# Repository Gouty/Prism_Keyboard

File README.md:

#  Prism Mechanical Keyboard

Prism is a low cost QMK compatable 60% + nav cluster (or TKL minus F-row if you prefer) keyboard.

It came about for a number of reasons:

 * I had some [TGW71 PCBs](https://www.reddit.com/r/MechanicalKeyboards/comments/5un33s/the_great_wave_custom_board/) designed by [u/ca178858](https://www.reddit.com/user/ca178858) lying around doing nothing
 * I am procrastinating instead of doing my PhD thesis writeup
 * There was a competition on [r/CustomKeyboards](https://www.reddit.com/r/CustomKeyboards/) to build retro themed keyboards.

As it was planned for the OG Summer competition I decided to emulate some of the design language of the [ZX Sepctrum](https://imgur.com/a/drfZssH) family of computers (particularly the the ones that came after the 48k).

## Initial Design document

## To Do

* Improve feet fastening/height adjustment
* Update .dxf to include latest revision

## Future Plans

Currently this repo is a bit of a dumping ground for what I have designed so far, though it is possible to recreate the keyboard entirely. Eventually I want it to include:

* Multiple plate layer configurations
* Multiple top layer configuations
* Changes to the PCB to include PCB mount stabilisers and better bottom row support

## Current status

Prototype complete - Displayed at Mechanical Keyboard Meetup (Leeds 26/10/2019)

## Posts about Prism

* [Initial](https://www.reddit.com/r/CustomKeyboards/comments/c7dlp8/ogsummer_zx_spectrum_inspired_work_in_progress/)
* [Update](https://www.reddit.com/r/CustomKeyboards/comments/cu45r6/ogsummer_prism_zx_spectrum_inspired_update/)
* [Keebtalk](https://www.keebtalk.com/t/prism-a-zx-spectrum-inspired-low-cost-acrylic-case/)
* [Prototype](https://www.reddit.com/r/MechanicalKeyboards/comments/dqqovr/rbgy/), [2](https://www.reddit.com/r/CustomKeyboards/comments/dqr5ce/prism_prototype/)

## Thanks

Original TGW71 PCB by [u/ca178858](https://www.reddit.com/user/ca178858) and [u/the_pokemon_kid](https://www.reddit.com/user/the_pokemon_kid)

Pixel art by Meowsaur

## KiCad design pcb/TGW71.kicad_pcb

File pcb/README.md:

# TGW71 PCB

Original files kindly provided by [u/ca178858](https://www.reddit.com/user/ca178858)

BOM:

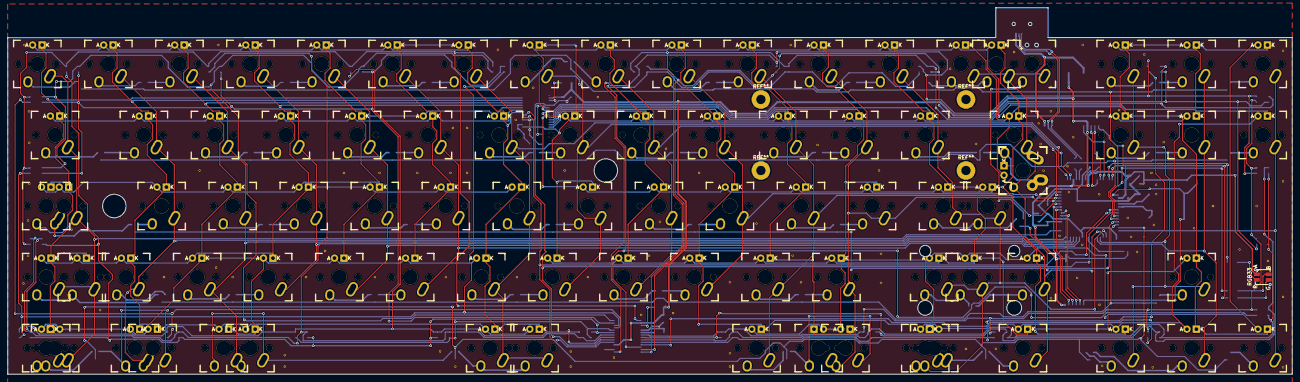
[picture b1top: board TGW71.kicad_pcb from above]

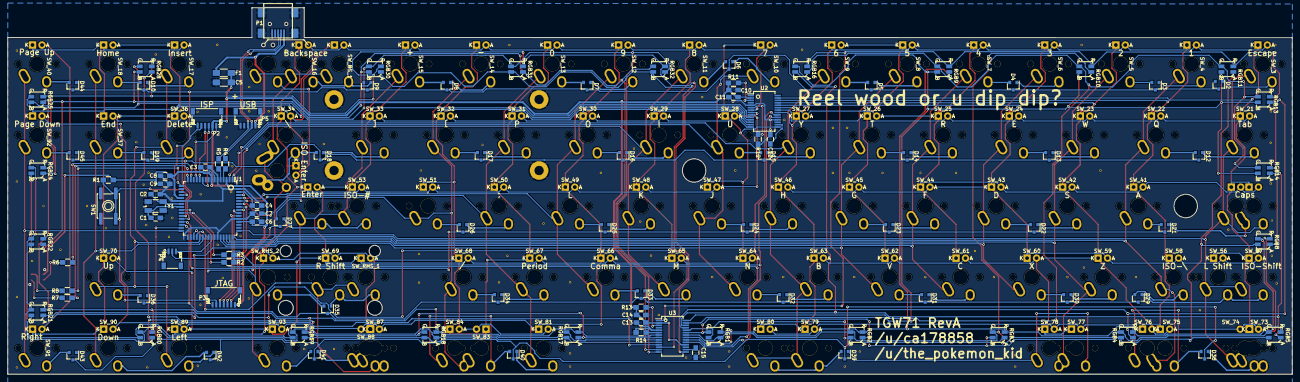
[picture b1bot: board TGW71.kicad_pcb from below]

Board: 2 copper layers, 344.5 x 98.3 mm, 192 parts (102 on the bottom side), 164 nets.

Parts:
C1, C2: 18pF; C_0805_HandSoldering
C3, C6, C7, C8, C9, C11, C12, C14, C15: 0.1µF; C_0805_HandSoldering
C4, C10, C13: 1µF; C_0805_HandSoldering
C5: 4.7µF; C_1206_HandSoldering
D2, D3, D4, D5, D6, D7, D8, D9, D10, D12, D13, D14, D15, D16, D17, D18, D19, D21, D22, D23, D24, D25, D26, D27, D29, D30, D31, D32, D33, D34, D35, D36, D38, D39, D40, D41, D42, D43, D44, D45: BAV70L; SOT-23
F1: FP_Small; C_1206_HandSoldering
P1: USB_OTG; USB_Mini-B
P2: CONN_02X03; JST_SH_SM06B-SRSS-TB_06x1.00mm_Angled
P3: CONN_01X07; JST_SH_SM07B-SRSS-TB_07x1.00mm_Angled
P4: CONN_01X03; JST_SH_SM03B-SRSS-TB_03x1.00mm_Angled
P5: CONN_01X05; JST_SH_SM05B-SRSS-TB_05x1.00mm_Angled
R1: 10kΩ; R_0805_HandSoldering
R2, R3: 4.7kΩ; R_0805_HandSoldering
R4, R5: 22Ω; R_0805_HandSoldering
R6: 150; R_0805_HandSoldering
R7, R8: 120; R_0805_HandSoldering
R11, R13: 10KΩ; R_0805_HandSoldering
R12, R14: 20KΩ; R_0805_HandSoldering
RGB1, RGB2, RGB3, RGB4, RGB5, RGB8, RGB9, RGB10, RGB11, RGB13, RGB14, RGB16, RGB17, RGB18, RGB19, RGB20, RGB21, RGB22, RGB24, RGB25, RGB28, RGB30, RGB31, RGB32: Led_RGB_CA; SMP4-RGB
RGB33: Led_RGB_CA; SMP4-RGB-PIPE
STA: Stabilizer; CHERRY_PCB_200_STABILIZER_OUTLINE
STA#2: Stabilizer; CHERRY_PCB_200_STABILIZER
SW1: SW_PUSH; SW_SPST_EVQP0
SW_3, SW_4, SW_5, SW_6, SW_7, SW_8, SW_9, SW_10, SW_11, SW_12, SW_13, SW_14, SW_15, SW_16, SW_17, SW_18, SW_21, SW_22, SW_23, SW_24, SW_25, SW_26, SW_27, SW_28, SW_29, SW_30, SW_31, SW_32, SW_33, SW_34, SW_35, SW_36, SW_37, SW_40, SW_41, SW_42, SW_43, SW_44, SW_45, SW_46, SW_47, SW_48, SW_49, SW_50, SW_51, SW_52, SW_53, SW_56, SW_57, SW_58, SW_59, SW_60, SW_61, SW_62, SW_63, SW_64, SW_65, SW_66, SW_67, SW_68, SW_69, SW_70, SW_73, SW_75, SW_76, SW_77, SW_78, SW_79, SW_80, SW_81, SW_84, SW_87, SW_89, SW_90, SW_91, SW_92, SW_93: MX_LED; MXALPS
SW_74, SW_83, SW_88: MX_LED; MXALPS_REVERSE_LED
SW_BS_1, SW_BS_2: MX_LED; MXALPS
SW_CAPS_1, SW_CAPS_2: MX_LED; MXALPS
SW_ISO_Alps_1: MX_LED; ALPS
SW_RHS_1, SW_RHS_2: MX_LED; MXALPS
U1: AT90USB1286-AU; TQFP-64_14x14mm_Pitch0.8mm
U2, U3: IS31FL3731; SSOP-28_5.3x10.2mm_Pitch0.65mm
Y1: CRYSTAL_SMD; Crystal_SMD_5032_4Pads

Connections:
+5V: C5.1, C6.1, C7.1, C8.1, C9.1, C10.1, C11.1, C13.1, C14.1, F1.2, P2.2, P3.1, P4.2, R1.1, R2.1, R3.1, R11.2, R13.2, RGB33.1, U1.3, U1.8, U1.21, U1.52, U1.64, U2.2, U3.2, U3.18
AUDIO: P4.3, U1.41
C3: SW_3.SW1, SW_21.SW1, SW_56.SW1, SW_57.SW1, SW_73.SW1, SW_74.SW1, SW_CAPS_1.SW2, SW_CAPS_2.SW1, U1.49
C4: SW_4.SW1, SW_22.SW1, SW_41.SW1, SW_58.SW1, SW_75.SW1, SW_76.SW2, U1.48
C5: SW_5.SW1, SW_23.SW1, SW_42.SW1, SW_59.SW1, SW_77.SW1, SW_78.SW2, U1.47
C6: SW_6.SW1, SW_24.SW1, SW_43.SW1, SW_60.SW1, U1.46
C7: SW_7.SW1, SW_25.SW1, SW_44.SW1, SW_61.SW1, U1.45
C8: SW_8.SW1, SW_26.SW1, SW_45.SW1, SW_62.SW1, U1.44
C9: SW_9.SW1, SW_27.SW1, SW_46.SW1, SW_63.SW1, SW_79.SW1, SW_80.SW1, U1.1
C10: SW_10.SW1, SW_28.SW1, SW_47.SW1, SW_64.SW1, U1.2
C11: SW_11.SW1, SW_29.SW1, SW_48.SW1, SW_65.SW1, U1.61
C12: SW_12.SW1, SW_30.SW1, SW_49.SW1, SW_66.SW1, U1.60
C13: SW_13.SW1, SW_31.SW1, SW_50.SW1, SW_67.SW1, SW_81.SW1, U1.59
C14: SW_14.SW1, SW_32.SW1, SW_51.SW1, SW_68.SW1, SW_83.SW1, SW_84.SW2, U1.58
C15: SW_15.SW1, SW_33.SW1, SW_52.SW1, SW_53.SW1, SW_69.SW1, SW_87.SW2, SW_88.SW2, SW_RHS_1.SW1, U1.35
C16: SW_16.SW1, SW_34.SW1, SW_35.SW1, SW_93.SW1, SW_BS_1.SW1, SW_BS_2.SW1, SW_ISO_Alps_1.SW2, SW_RHS_2.SW1, U1.36
C17: SW_17.SW1, SW_36.SW1, SW_70.SW1, SW_89.SW1, U1.37
C18: SW_18.SW1, SW_37.SW1, SW_90.SW1, U1.38
C19: SW_40.SW1, SW_91.SW1, SW_92.SW1, U1.32
D+: R5.1, U1.5
D-: R4.1, U1.4
GND: C1.2, C2.2, C3.2, C4.2, C5.2, C6.2, C7.2, C8.2, C9.2, C10.2, C11.2, C12.2, C13.2, C14.2, C15.2, P1.5, P1.6, P2.6, P3.7, P4.1, P5.5, R12.2, R14.2, SW1.1, U1.6, U1.22, U1.43, U1.53, U1.63, U2.5, U2.18, U3.5, Y1.3
LED_SCL: R2.2, U1.25, U2.20, U3.20
LED_SDA: R3.2, U1.26, U2.19, U3.19
L_CA1: SW_3.A, SW_4.A, SW_5.A, SW_6.A, SW_7.A, SW_8.A, SW_9.K, SW_27.K, SW_46.K, SW_63.K, SW_79.K, SW_80.K, U2.21
L_CA2: SW_8.K, SW_9.A, SW_21.A, SW_22.A, SW_23.A, SW_24.A, SW_25.A, SW_26.K, SW_45.K, SW_62.K, U2.22
L_CA3: SW_7.K, SW_25.K, SW_26.A, SW_27.A, SW_41.A, SW_42.A, SW_43.A, SW_44.K, SW_61.K, SW_CAPS_1.A, SW_CAPS_2.A, U2.23
L_CA4: SW_6.K, SW_24.K, SW_43.K, SW_44.A, SW_45.A, SW_46.A, SW_56.A, SW_57.A, SW_58.A, SW_59.A, SW_60.K, U2.24
L_CA5: SW_5.K, SW_23.K, SW_42.K, SW_59.K, SW_60.A, SW_61.A, SW_62.A, SW_63.A, SW_73.A, SW_74.A, SW_75.A, SW_76.A, SW_77.K, SW_78.K, U2.25
L_CA6: SW_4.K, SW_22.K, SW_41.K, SW_58.K, SW_75.K, SW_76.K, SW_77.A, SW_78.A, SW_79.A, SW_80.A, U2.26
L_CA7: SW_3.K, SW_21.K, SW_56.K, SW_57.K, SW_73.K, SW_74.K, SW_CAPS_1.K, SW_CAPS_2.K, U2.27
L_CB1: SW_10.A, SW_11.A, SW_12.A, SW_13.A, SW_14.A, SW_15.A, SW_16.A, SW_17.A, SW_18.K, SW_37.K, SW_40.K, SW_92.K, SW_BS_1.A, U2.7
L_CB2: SW_17.K, SW_18.A, SW_28.A, SW_29.A, SW_30.A, SW_31.A, SW_32.A, SW_33.A, SW_34.A, SW_35.A, SW_36.K, SW_70.K, SW_90.K, SW_91.K, SW_BS_1.K, U2.8
L_CB3: SW_16.K, SW_34.K, SW_35.K, SW_36.A, SW_37.A, SW_47.A, SW_48.A, SW_49.A, SW_50.A, SW_51.A, SW_52.K, SW_53.A, SW_89.K, SW_RHS_2.K, U2.9
L_CB4: SW_15.K, SW_33.K, SW_52.A, SW_53.K, SW_64.A, SW_65.A, SW_66.A, SW_67.A, SW_68.A, SW_69.K, SW_70.A, SW_93.K, SW_RHS_1.K, U2.10
L_CB5: SW_14.K, SW_32.K, SW_40.A, SW_51.K, SW_68.K, SW_69.A, SW_81.A, SW_83.A, SW_84.A, SW_87.K, SW_88.K, SW_91.A, SW_RHS_1.A, SW_RHS_2.A, U2.11
L_CB6: SW_13.K, SW_31.K, SW_50.K, SW_67.K, SW_83.K, SW_84.K, U2.12
L_CB7: SW_12.K, SW_30.K, SW_49.K, SW_66.K, SW_81.K, SW_87.A, SW_88.A, SW_89.A, SW_90.A, SW_92.A, SW_93.A, U2.13
L_CB8: SW_11.K, SW_29.K, SW_48.K, SW_65.K, U2.14
L_CB9: SW_10.K, SW_28.K, SW_47.K, SW_64.K, U2.15
MISO: P2.1, U1.13
MOSI: P2.4, U1.12
unnamed: C1.1, U1.24, Y1.1
unnamed: C2.1, U1.23, Y1.2
unnamed: C3.1, U1.7
unnamed: C4.1, U1.62
unnamed: C12.1, U2.16
unnamed: C15.1, U3.16
unnamed: D2.1, SW_3.SW2
unnamed: D3.1, SW_4.SW2
unnamed: D3.2, SW_5.SW2
unnamed: D4.1, SW_6.SW2
unnamed: D4.2, SW_7.SW2
unnamed: D5.1, SW_8.SW2
unnamed: D5.2, SW_9.SW2
unnamed: D6.1, SW_10.SW2
unnamed: D6.2, SW_11.SW2
unnamed: D7.1, SW_12.SW2
unnamed: D7.2, SW_13.SW2
unnamed: D8.1, SW_14.SW2
unnamed: D8.2, SW_15.SW2
unnamed: D9.1, SW_16.SW2, SW_BS_1.SW2
unnamed: D10.1, SW_17.SW2
unnamed: D10.2, SW_18.SW2
unnamed: D12.1, SW_21.SW2
unnamed: D12.2, SW_22.SW2
unnamed: D13.1, SW_23.SW2
unnamed: D13.2, SW_24.SW2
unnamed: D14.1, SW_25.SW2
unnamed: D14.2, SW_26.SW2
unnamed: D15.1, SW_27.SW2
unnamed: D15.2, SW_28.SW2
unnamed: D16.1, SW_29.SW2
unnamed: D16.2, SW_30.SW2
unnamed: D17.1, SW_31.SW2
unnamed: D17.2, SW_32.SW2
unnamed: D18.1, SW_33.SW2
unnamed: D18.2, SW_34.SW2, SW_35.SW2, SW_ISO_Alps_1.SW1
unnamed: D19.1, SW_36.SW2
unnamed: D19.2, SW_37.SW2
unnamed: D21.1, SW_CAPS_1.SW1, SW_CAPS_2.SW2
unnamed: D21.2, SW_41.SW2
unnamed: D22.1, SW_42.SW2
unnamed: D22.2, SW_43.SW2
unnamed: D23.1, SW_44.SW2
unnamed: D23.2, SW_45.SW2
unnamed: D24.1, SW_46.SW2
unnamed: D24.2, SW_47.SW2
unnamed: D25.1, SW_48.SW2
unnamed: D25.2, SW_49.SW2
unnamed: D26.1, SW_50.SW2
unnamed: D26.2, SW_51.SW2
unnamed: D27.1, SW_52.SW2, SW_53.SW2
unnamed: D27.2, SW_BS_2.SW2
unnamed: D29.1, SW_56.SW2, SW_57.SW2
unnamed: D29.2, SW_58.SW2
unnamed: D30.1, SW_59.SW2
unnamed: D30.2, SW_60.SW2
unnamed: D31.1, SW_61.SW2
unnamed: D31.2, SW_62.SW2
unnamed: D32.1, SW_63.SW2
unnamed: D32.2, SW_64.SW2
unnamed: D33.1, SW_65.SW2
unnamed: D33.2, SW_66.SW2
unnamed: D34.1, SW_67.SW2
unnamed: D34.2, SW_68.SW2
unnamed: D35.1, SW_69.SW2, SW_RHS_1.SW2
unnamed: D35.2, SW_RHS_2.SW2
unnamed: D36.2, SW_70.SW2
unnamed: D38.1, SW_73.SW2, SW_74.SW2
unnamed: D38.2, SW_75.SW2, SW_76.SW1
unnamed: D39.1, SW_77.SW2, SW_78.SW1
unnamed: D39.2, SW_79.SW2, SW_80.SW2
unnamed: D40.1, SW_81.SW2
unnamed: D40.2, SW_83.SW2, SW_84.SW1
unnamed: D41.1, SW_87.SW1, SW_88.SW1
unnamed: D41.2, SW_93.SW2
unnamed: D42.1, SW_89.SW2
unnamed: D42.2, SW_90.SW2
unnamed: D43.2, SW_91.SW2
unnamed: D44.2, SW_40.SW2
unnamed: D45.2, SW_92.SW2
unnamed: R6.1, RGB33.2
unnamed: R7.1, RGB33.3
unnamed: R8.1, RGB33.4
unnamed: R11.1, U2.3
unnamed: R12.1, U2.6
unnamed: R13.1, U3.3
unnamed: R14.1, U3.6
PWM_BLUE: R8.2, U1.17
PWM_GREEN: R7.2, U1.16
PWM_RED: R6.2, U1.15
R1: D2.3, D3.3, D4.3, D5.3, D6.3, D7.3, D8.3, D9.3, D10.3, D44.3, U1.27
R2: D12.3, D13.3, D14.3, D15.3, D16.3, D17.3, D18.3, D19.3, D45.3, U1.28
R3: D21.3, D22.3, D23.3, D24.3, D25.3, D26.3, D27.3, U1.29
R4: D29.3, D30.3, D31.3, D32.3, D33.3, D34.3, D35.3, D36.3, U1.30
R5: D38.3, D39.3, D40.3, D41.3, D42.3, D43.3, U1.31
RESET: P2.5, P3.6, R1.2, SW1.2, U1.20
R_CA1: RGB1.2, RGB2.2, RGB3.2, RGB4.2, RGB5.2, RGB8.2, RGB9.1, U3.21
R_CA2: RGB1.1, RGB2.3, RGB3.3, RGB4.3, RGB5.3, RGB8.3, RGB10.1, U3.22
R_CA3: RGB1.3, RGB2.1, RGB3.4, RGB4.4, RGB5.4, RGB8.4, RGB11.1, U3.23
R_CA4: RGB1.4, RGB2.4, RGB3.1, U3.24
R_CA5: RGB4.1, RGB13.1, U3.25
R_CA6: RGB5.1, RGB14.1, RGB16.4, U3.26
R_CA7: RGB9.4, RGB10.4, RGB11.4, RGB13.4, RGB14.4, RGB16.3, U3.27
R_CA8: RGB9.3, RGB10.3, RGB11.3, RGB13.3, RGB14.3, RGB16.1, U3.28
R_CA9: RGB8.1, RGB9.2, RGB10.2, RGB11.2, RGB13.2, RGB14.2, RGB16.2, U3.1
R_CB1: RGB17.2, RGB18.2, RGB19.2, RGB20.2, RGB21.2, RGB22.2, RGB24.2, RGB25.1, U3.7
R_CB2: RGB17.1, RGB18.3, RGB19.3, RGB20.3, RGB21.3, RGB22.3, RGB24.3, U3.8
R_CB3: RGB17.3, RGB18.1, RGB19.4, RGB20.4, RGB21.4, RGB22.4, RGB24.4, U3.9
R_CB4: RGB17.4, RGB18.4, RGB19.1, RGB28.1, U3.10
R_CB5: RGB20.1, U3.11
R_CB6: RGB21.1, RGB30.1, RGB31.4, RGB32.4, U3.12
R_CB7: RGB22.1, RGB25.4, RGB28.4, RGB30.4, RGB31.1, RGB32.3, U3.13
R_CB8: RGB25.3, RGB28.3, RGB30.3, RGB31.3, RGB32.1, U3.14
R_CB9: RGB24.1, RGB25.2, RGB28.2, RGB30.2, RGB31.2, RGB32.2, U3.15
SCK: P2.3, U1.11
TCK: P3.2, U1.57
TDI: P3.5, U1.54
TDO: P3.4, U1.55
TMS: P3.3, U1.56
USB+: P1.3, P5.3, R5.2
USB-: P1.2, P5.2, R4.2
VBUS: F1.1, P1.1, P5.1

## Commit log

2019-10-25 Updating front page
2019-10-25 Improved images
2019-10-25 Fixing bulletpoints
2019-10-25 Added PCB Files
2019-10-25 Add case files
    v1 of case files, kerf applied is 0.15 (too tight on the vertical bits currently)
2019-10-25 Added some firmware bits (incomplete)
2019-11-03 Added Photos
2019-11-03 Hopefully fixed photos
2019-11-03 change capitalisation of folder
2019-11-04 Removed broken .dxf, updated readme
2019-12-20 Changes to case and pixel art
2019-12-20 Readme Header fix
2019-12-20 Added thanks to Readme
